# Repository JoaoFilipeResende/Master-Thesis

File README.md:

# Master Thesis Project
## Autonomous High-Resolution Image Acquisition System for Plankton

### System Architecture

a) BMS; b) Battery; c) External Connection; d) SBC; e) Storage; f) Camera; g) Optical lens; h) Illumination system control board; i) Water Column; j) Organism; k) LEDs.
   
### Mechanical Structure

### Hardware

### Software

### Experimental Results

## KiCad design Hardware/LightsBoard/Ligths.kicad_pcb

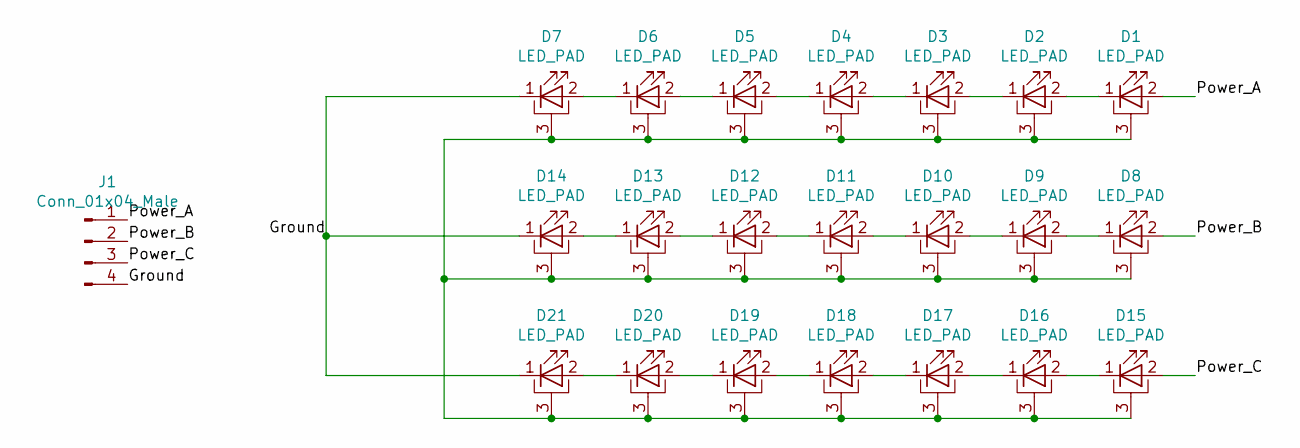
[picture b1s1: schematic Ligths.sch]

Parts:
D1, D2, D3, D4, D5, D6, D7, D8, D9, D10, D11, D12, D13, D14, D15, D16, D17, D18, D19, D20, D21: LED_PAD; LED_Cree-XP
J1: Conn_01x04_Male; Molex_SPOX_5267-04A_1x04_P2.50mm_Vertical

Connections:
/Ground: D7.1 (K), D14.1 (K), D21.1 (K), J1.4
/Power_A: D1.2 (A), J1.1
/Power_B: D8.2 (A), J1.2
/Power_C: D15.2 (A), J1.3
unnamed: D1.1 (K), D2.2 (A)
unnamed: D1.3 (PAD), D2.3 (PAD), D3.3 (PAD), D4.3 (PAD), D5.3 (PAD), D6.3 (PAD), D7.3 (PAD), D8.3 (PAD), D9.3 (PAD), D10.3 (PAD), D11.3 (PAD), D12.3 (PAD), D13.3 (PAD), D14.3 (PAD), D15.3 (PAD), D16.3 (PAD), D17.3 (PAD), D18.3 (PAD), D19.3 (PAD), D20.3 (PAD), D21.3 (PAD)
unnamed: D2.1 (K), D3.2 (A)
unnamed: D3.1 (K), D4.2 (A)
unnamed: D4.1 (K), D5.2 (A)
unnamed: D5.1 (K), D6.2 (A)
unnamed: D6.1 (K), D7.2 (A)
unnamed: D8.1 (K), D9.2 (A)
unnamed: D10.1 (K), D11.2 (A)
unnamed: D9.1 (K), D10.2 (A)
unnamed: D11.1 (K), D12.2 (A)
unnamed: D12.1 (K), D13.2 (A)
unnamed: D13.1 (K), D14.2 (A)
unnamed: D15.1 (K), D16.2 (A)
unnamed: D16.1 (K), D17.2 (A)
unnamed: D17.1 (K), D18.2 (A)
unnamed: D18.1 (K), D19.2 (A)
unnamed: D19.1 (K), D20.2 (A)
unnamed: D20.1 (K), D21.2 (A)

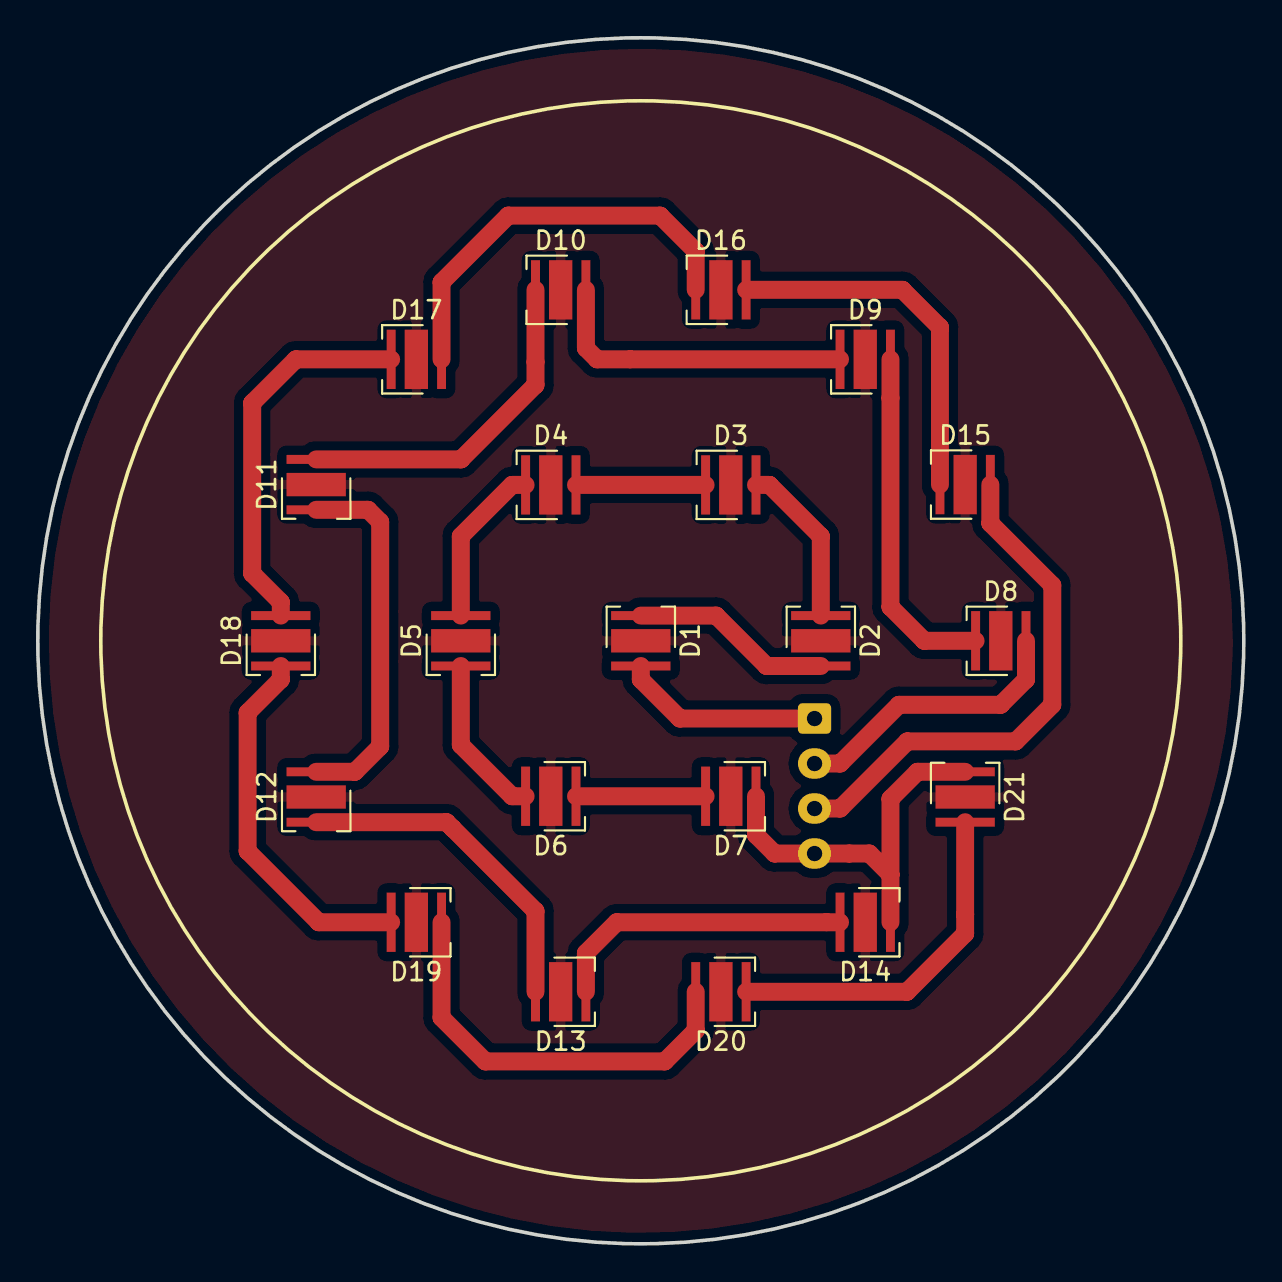
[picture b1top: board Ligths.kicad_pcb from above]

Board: 2 copper layers, 67.0 x 67.0 mm, 22 parts (1 on the bottom side), 23 nets.

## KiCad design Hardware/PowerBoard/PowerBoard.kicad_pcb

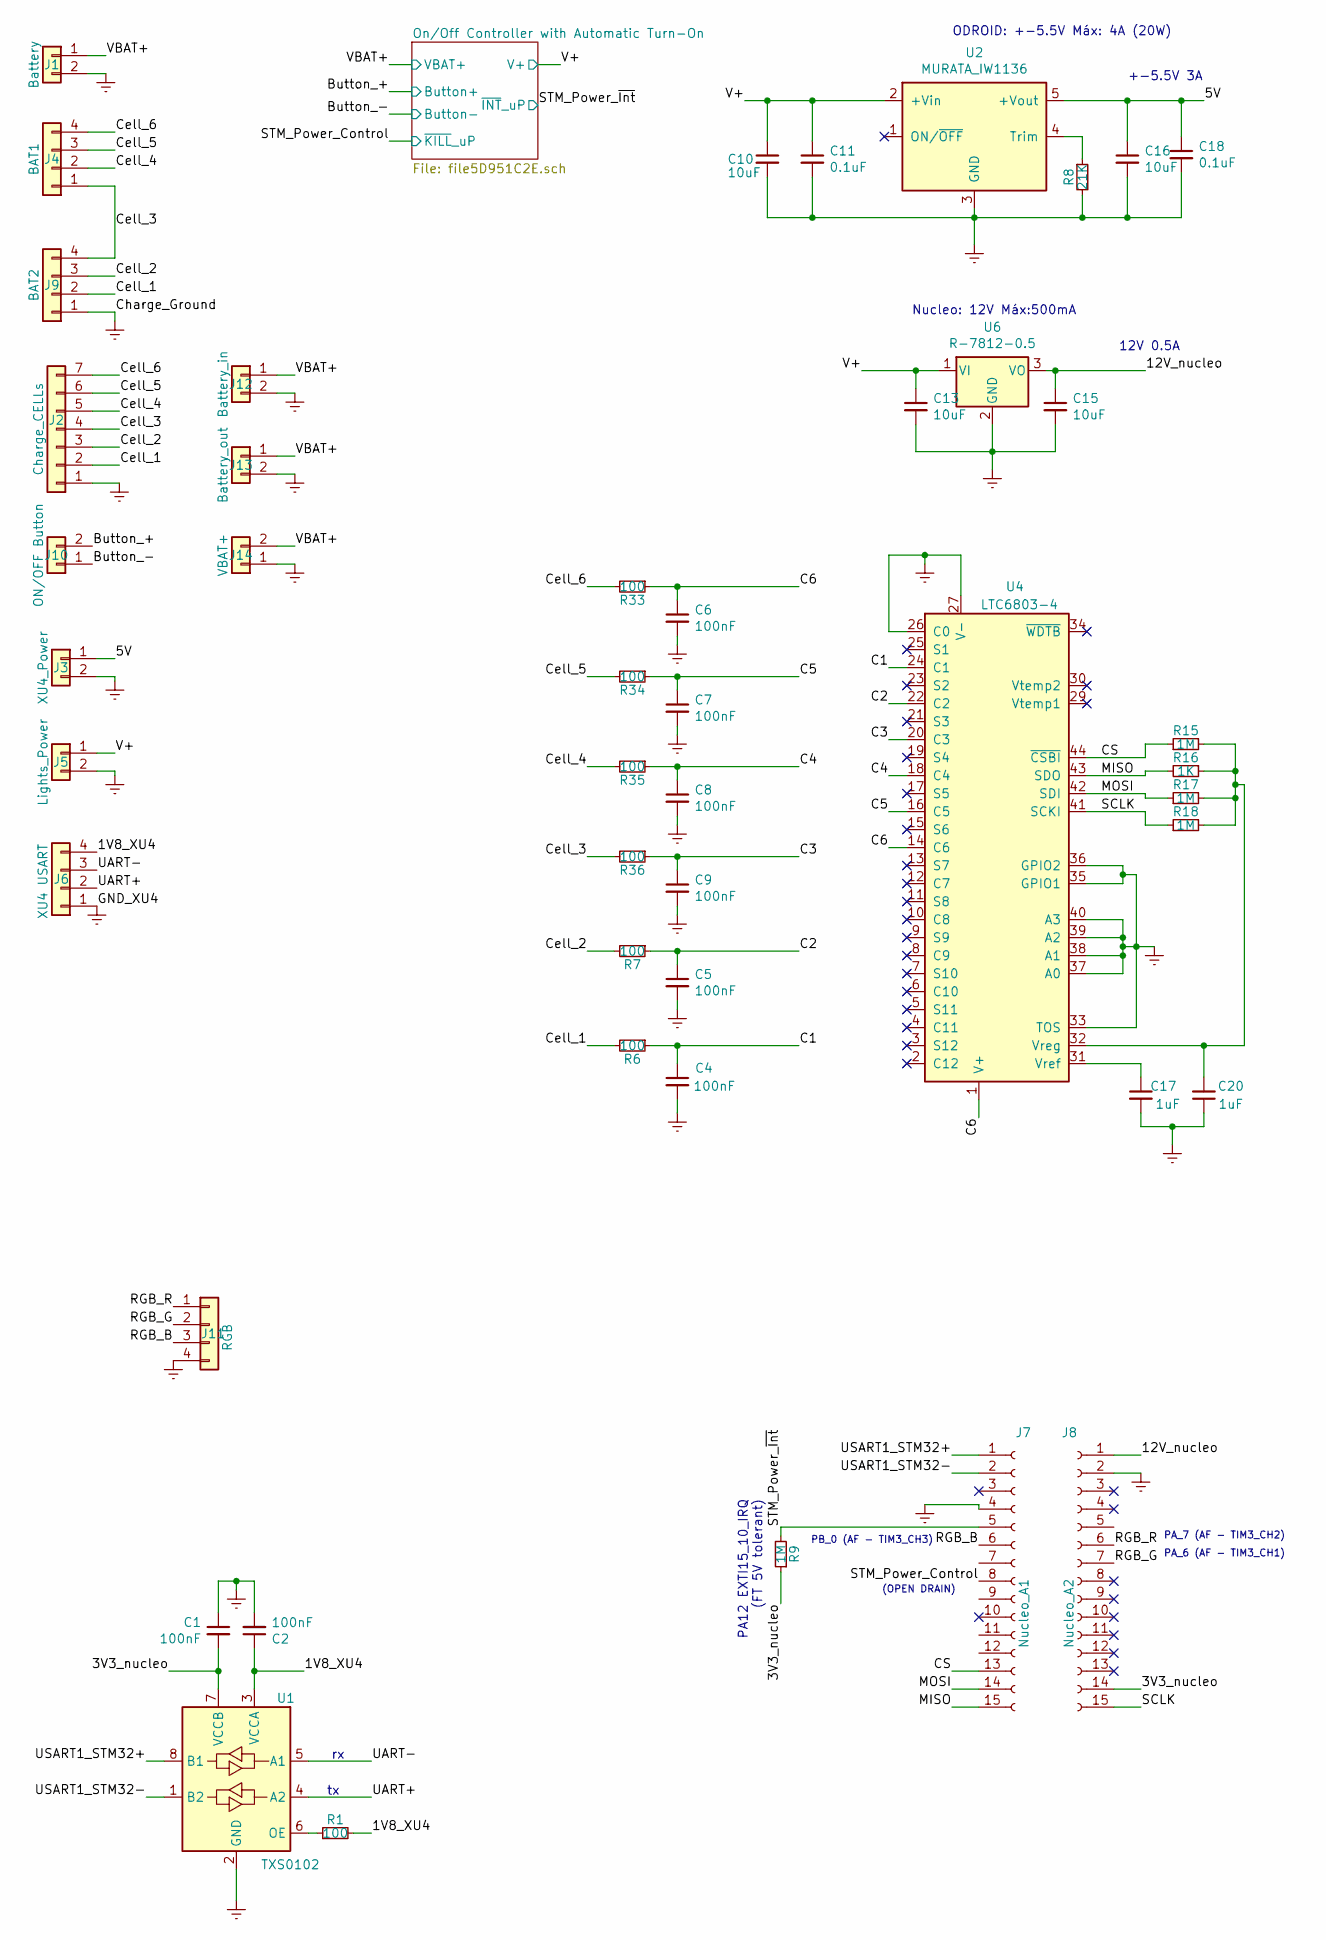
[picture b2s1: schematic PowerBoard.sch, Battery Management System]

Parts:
C1, C2, C4, C5, C6, C7, C8, C9: 100nF; C_0805_2012Metric_Pad1.15x1.40mm_HandSolder
C10, C13, C15, C16: 10uF; C_0805_2012Metric_Pad1.15x1.40mm_HandSolder
C11, C18: 0.1uF; C_0805_2012Metric_Pad1.15x1.40mm_HandSolder
C17, C20: 1uF; C_0805_2012Metric_Pad1.15x1.40mm_HandSolder
J1: Battery; Hirose_DF63-2P-3.96DSA_1x02_P3.96mm_Horizontal
J2: Charge_CELLs; JST_EH_B07B-EH-A_1x07_P2.50mm_Vertical
J3: XU4_Power; Hirose_DF63-2P-3.96DSA_1x02_P3.96mm_Horizontal
J4: BAT1; JST_EH_B04B-EH-A_1x04_P2.50mm_Vertical
J5: Lights_Power; Hirose_DF63-2P-3.96DSA_1x02_P3.96mm_Horizontal
J6: XU4 USART; JST_GH_SM04B-GHS-TB_1x04-1MP_P1.25mm_Horizontal
J7: Nucleo_A1; PinSocket_1x15_P2.54mm_Vertical_SMD_Pin1Left
J8: Nucleo_A2; PinSocket_1x15_P2.54mm_Vertical_SMD_Pin1Left
J9: BAT2; JST_EH_B04B-EH-A_1x04_P2.50mm_Vertical
J10: ON/OFF Button; Molex_SPOX_5267-02A_1x02_P2.50mm_Vertical
J11: RGB; JST_GH_SM04B-GHS-TB_1x04-1MP_P1.25mm_Horizontal
J12: Battery_in; Hirose_DF63-2P-3.96DSA_1x02_P3.96mm_Horizontal
J13: Battery_out; Hirose_DF63-2P-3.96DSA_1x02_P3.96mm_Horizontal
J14: VBAT+; Molex_SPOX_5267-02A_1x02_P2.50mm_Vertical
R1, R6, R7, R33, R34, R35, R36: 100; R_0805_2012Metric_Pad1.15x1.40mm_HandSolder
R8: 21K; R_0805_2012Metric_Pad1.15x1.40mm_HandSolder
R9, R15, R17, R18: 1M; R_0805_2012Metric_Pad1.15x1.40mm_HandSolder
R16: 1K; R_0805_2012Metric_Pad1.15x1.40mm_HandSolder
U1: TXS0102; VSSOP-8_3.0x3.0mm_P0.65mm
U2: MURATA_IW1136; IW1136
U4: LTC6803-4; SSOP-44_5.3x12.8mm_P0.5mm
U6: R-7812-0.5; Converter_DCDC_RECOM_R-78E-0.5_THT

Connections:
/1V8_XU4: C2.1, J6.4, R1.2, U1.3 (VCCA)
/3V3_nucleo: C1.2, J8.14, R9.1, U1.7 (VCCB)
/5V: C16.1, C18.1, J3.1, U2.5 (+Vout)
/12V_nucleo: C15.1, J8.1, U6.3 (VO)
/Button_+: J1.1, J10.2, J12.1, J13.1, J14.2; also elsewhere on the board
/Button_-: J10.1; also elsewhere on the board
/C1: C4.1, R6.1, U4.24 (C1)
/C2: C5.1, R7.1, U4.22 (C2)
/C3: C9.1, R36.1, U4.20 (C3)
/C4: C8.1, R35.1, U4.18 (C4)
/C5: C7.1, R34.1, U4.16 (C5)
/C6: C6.1, R33.1, U4.1 (V+), U4.14 (C6)
/CS: J7.13, R15.1, U4.44 (~CSBI~)
/Cell_1: J2.2, J9.2, R6.2
/Cell_2: J2.3, J9.3, R7.2
/Cell_3: J2.4, J4.1, J9.4, R36.2
/Cell_4: J2.5, J4.2, R35.2
/Cell_5: J2.6, J4.3, R34.2
/Cell_6: J2.7, J4.4, R33.2
/MISO: J7.15, R16.2, U4.43 (SDO)
/MOSI: J7.14, R17.1, U4.42 (SDI)
/RGB_B: J7.6, J11.3
/RGB_G: J8.7, J11.2
/RGB_R: J8.6, J11.1
/SCLK: J8.15, R18.1, U4.41 (SCKI)
/STM_Power_Control: J7.8; also elsewhere on the board
/STM_Power_~Int~: J7.5, R9.2; also elsewhere on the board
/UART+: J6.2, U1.4 (A2)
/UART-: J6.3, U1.5 (A1)
/USART1_STM32+: J7.1, U1.8 (B1)
/USART1_STM32-: J7.2, U1.1 (B2)
/V+: C10.1, C11.1, C13.1, J5.1, U2.2 (+Vin), U6.1 (VI); also elsewhere on the board
Earth: C1.1, C2.2, C4.2, C5.2, C6.2, C7.2, C8.2, C9.2, C10.2, C11.2, C13.2, C15.2, C16.2, C17.2, C18.2, C20.1, J1.2, J2.1, J3.2, J5.2, J6.1, J7.4, J8.2, J9.1, J11.4, J12.2, J13.2, J14.1, R8.2, U1.2 (GND), U2.3 (GND), U4.26 (C0), U4.27 (V-), U4.33 (TOS), U4.35 (GPIO1), U4.36 (GPIO2), U4.37 (A0), U4.38 (A1), U4.39 (A2), U4.40 (A3), U6.2 (GND); also elsewhere on the board
unnamed: C17.1, U4.31 (Vref)
unnamed: C20.2, R15.2, R16.1, R17.2, R18.2, U4.32 (Vreg)
unnamed: R1.1, U1.6 (OE)
unnamed: R8.1, U2.4 (Trim)

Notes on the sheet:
ODROID: +-5.5V Máx: 4A (20W)
Nucleo: 12V Máx:500mA
12V 0.5A
+-5.5V 3A
PB_0 (AF - TIM3_CH3)
PA_7 (AF - TIM3_CH2)
PA_6 (AF - TIM3_CH1)
PA12 EXTI15_10_IRQ (FT 5V tolerant)
(OPEN DRAIN)

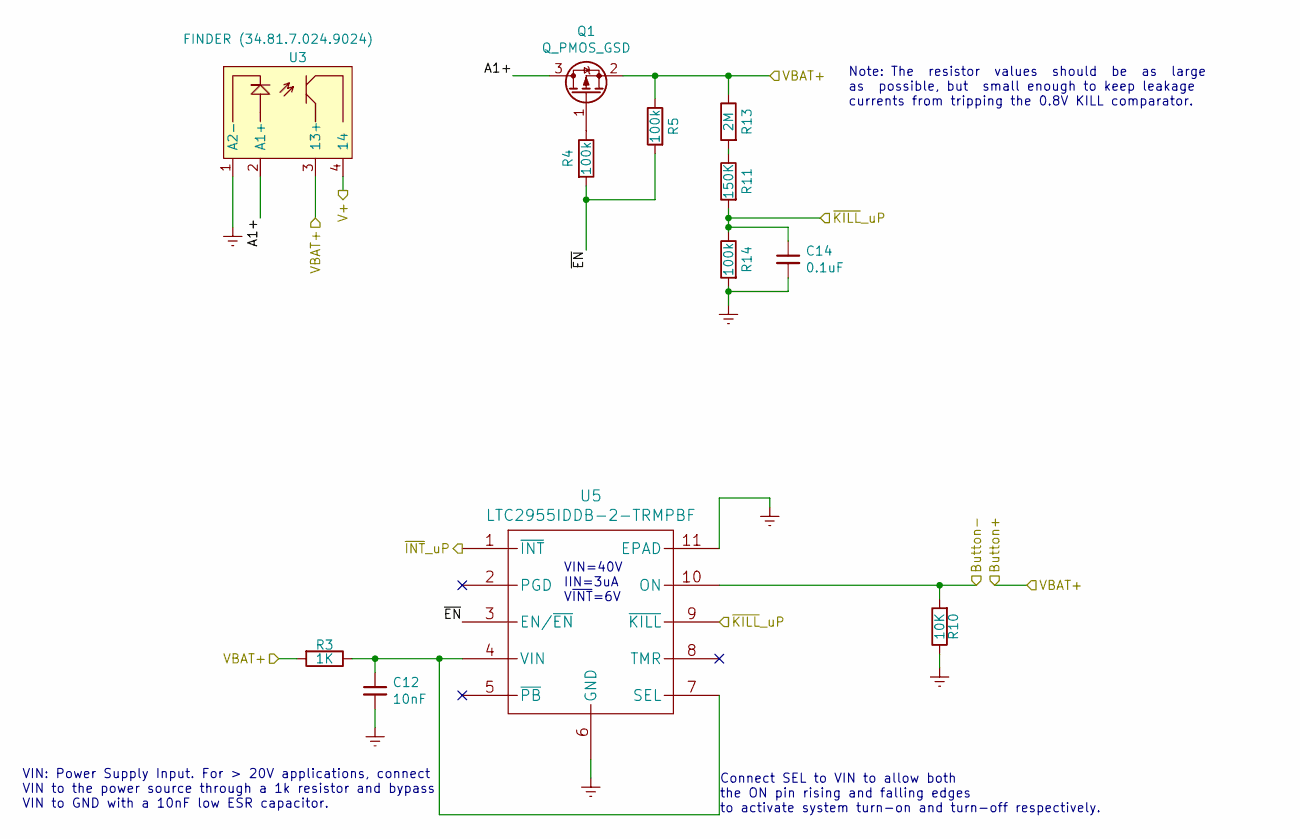
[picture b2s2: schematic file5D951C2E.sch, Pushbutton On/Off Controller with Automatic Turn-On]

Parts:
C12: 10nF; C_0805_2012Metric_Pad1.15x1.40mm_HandSolder
C14: 0.1uF; C_0805_2012Metric_Pad1.15x1.40mm_HandSolder
Q1: Q_PMOS_GSD; TSOT-23_HandSoldering
R3: 1K; R_0805_2012Metric_Pad1.15x1.40mm_HandSolder
R4, R5, R14: 100k; R_0805_2012Metric_Pad1.15x1.40mm_HandSolder
R10: 10K; R_0805_2012Metric_Pad1.15x1.40mm_HandSolder
R11: 150K; R_0805_2012Metric_Pad1.15x1.40mm_HandSolder
R13: 2M; R_0805_2012Metric_Pad1.15x1.40mm_HandSolder
U3: FINDER (34.81.7.024.9024); Relay_SPDT_Finder_34.81_Vertical
U5: LTC2955IDDB-2-TRMPBF; DFN-10-1EP_2x3mm_P0.5mm_EP0.64x2.4mm

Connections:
/Button_+: Q1.2 (S), R3.2, R5.1, R13.1, U3.3 (13+); also elsewhere on the board
/Button_-: R10.2, U5.10 (ON); also elsewhere on the board
/On/Off Controller with Automatic Turn-On/A1+: Q1.3 (D), U3.2 (A1+)
/On/Off Controller with Automatic Turn-On/~EN: R4.2, R5.2, U5.3 (EN/~EN)
/STM_Power_Control: C14.1, R11.2, R14.1, U5.9 (~KILL); also elsewhere on the board
/STM_Power_~Int~: U5.1 (~INT); also elsewhere on the board
/V+: U3.4 (14); also elsewhere on the board
Earth: C12.2, C14.2, R10.1, R14.2, U3.1 (A2-), U5.6 (GND), U5.11 (EPAD); also elsewhere on the board
unnamed: C12.1, R3.1, U5.4 (VIN), U5.7 (SEL)
unnamed: Q1.1 (G), R4.1
unnamed: R11.1, R13.2

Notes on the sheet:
VIN=40V IIN=3uA V~INT~=6V
Note: The resistor values should be as large as possible, but small enough to keep leakage currents from tripping the 0.8V KILL comparator.
VIN: Power Supply Input. For > 20V applications, connect VIN to the power source through a 1k resistor and bypass VIN to GND with a 10nF low ESR capacitor.
Connect SEL to VIN to allow both the ON pin rising and falling edges to activate system turn-on and turn-off respectively.

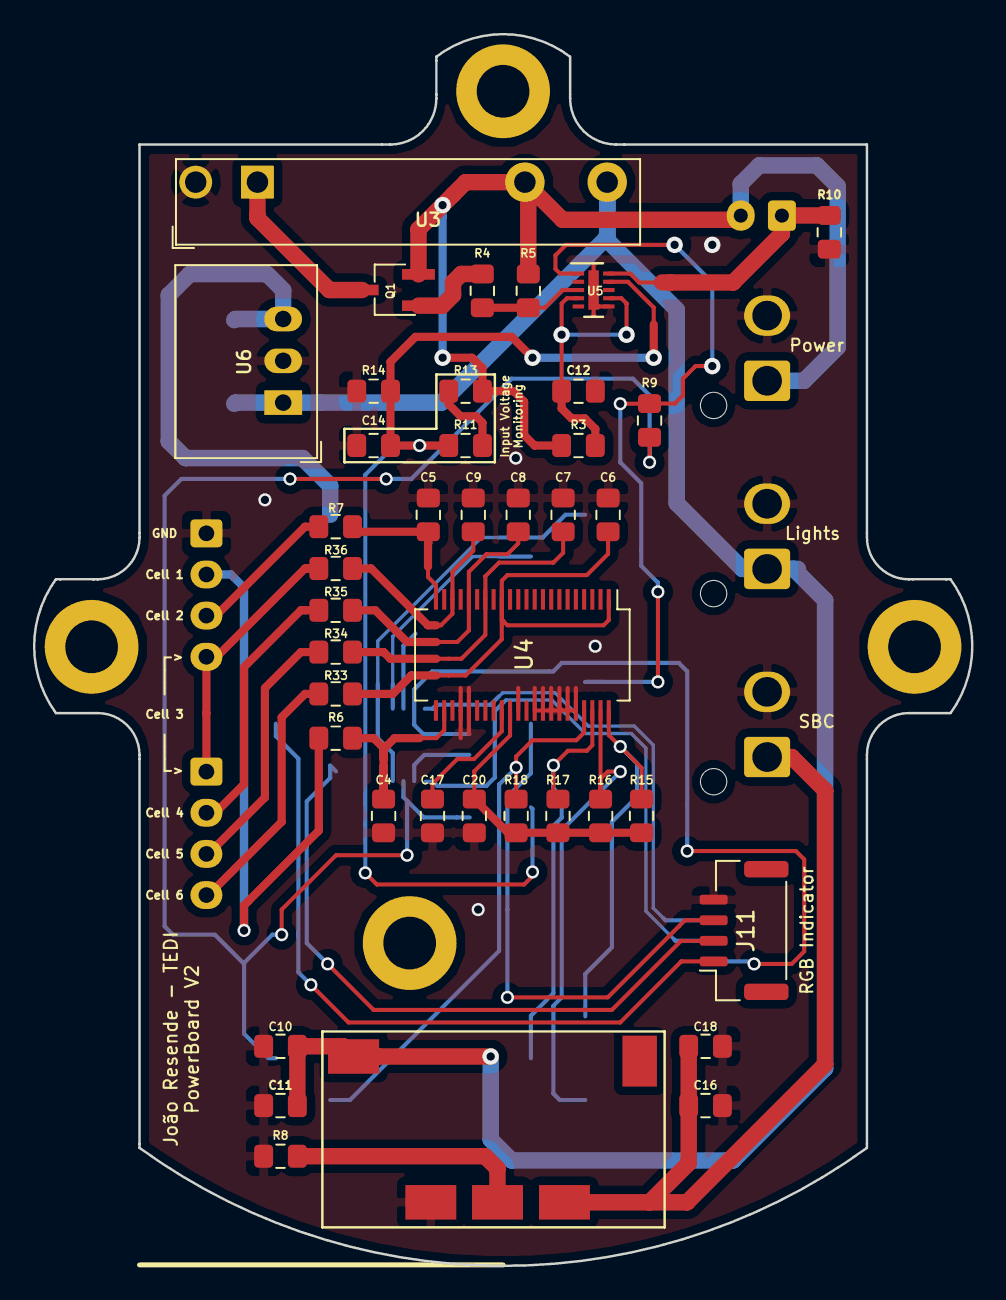
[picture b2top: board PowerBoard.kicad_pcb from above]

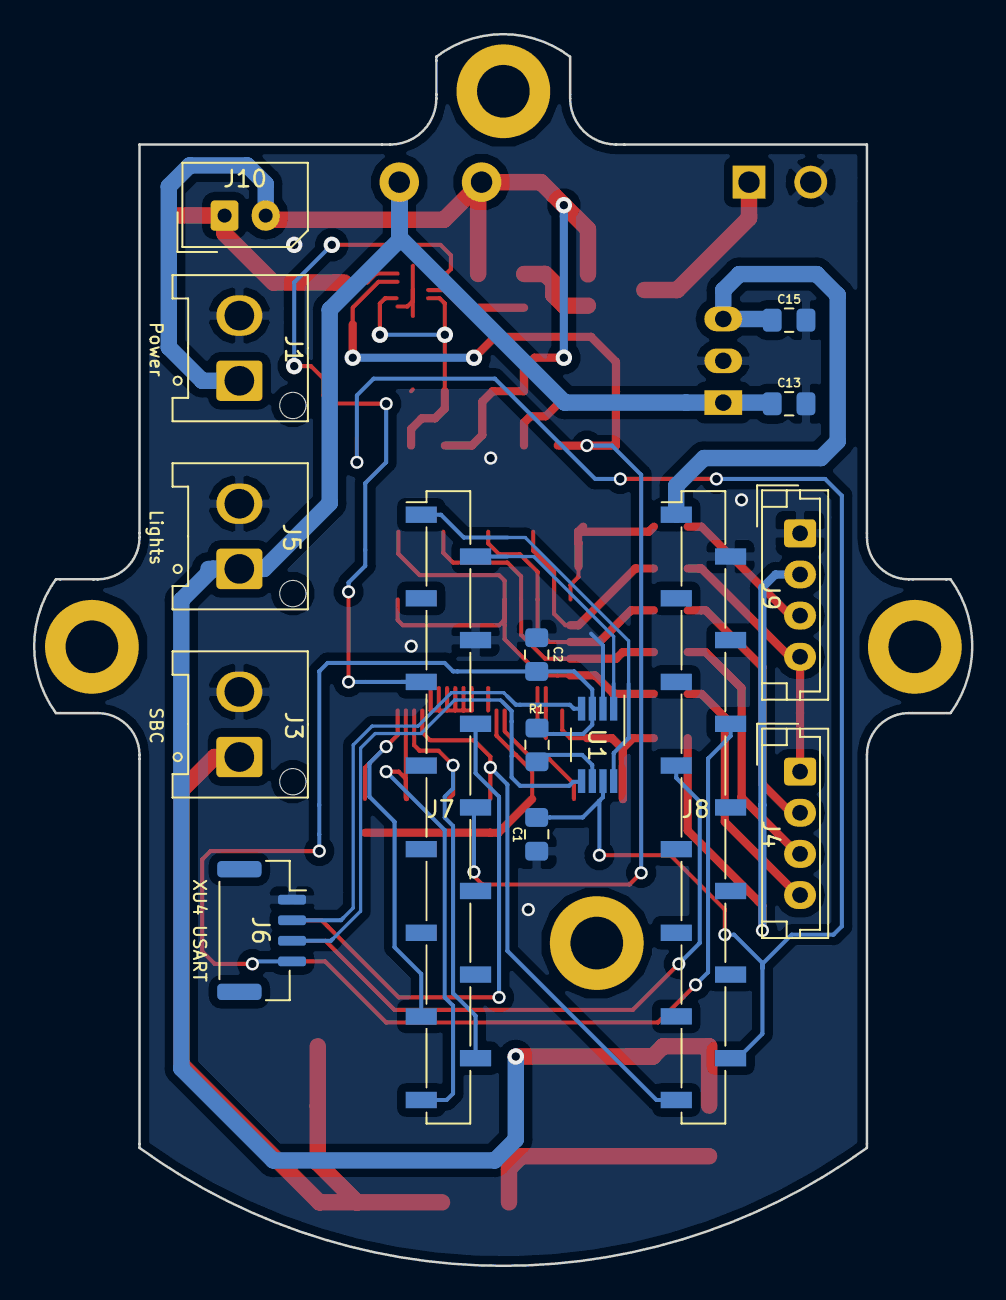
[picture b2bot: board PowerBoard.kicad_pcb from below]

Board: 2 copper layers, 57.0 x 74.8 mm, 55 parts (15 on the bottom side), 42 nets.

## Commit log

2022-01-28 added 3D drawings of the mechanical parts
2022-01-28 added gif version of the final_assembly.mp4
2022-01-29 added experimental results
2022-01-30 added powerboard project
2022-01-31 added 3D animation of the Powerboard
2022-01-31 added Powerboard software (STM32F303K8)
2022-01-31 added illumination board
